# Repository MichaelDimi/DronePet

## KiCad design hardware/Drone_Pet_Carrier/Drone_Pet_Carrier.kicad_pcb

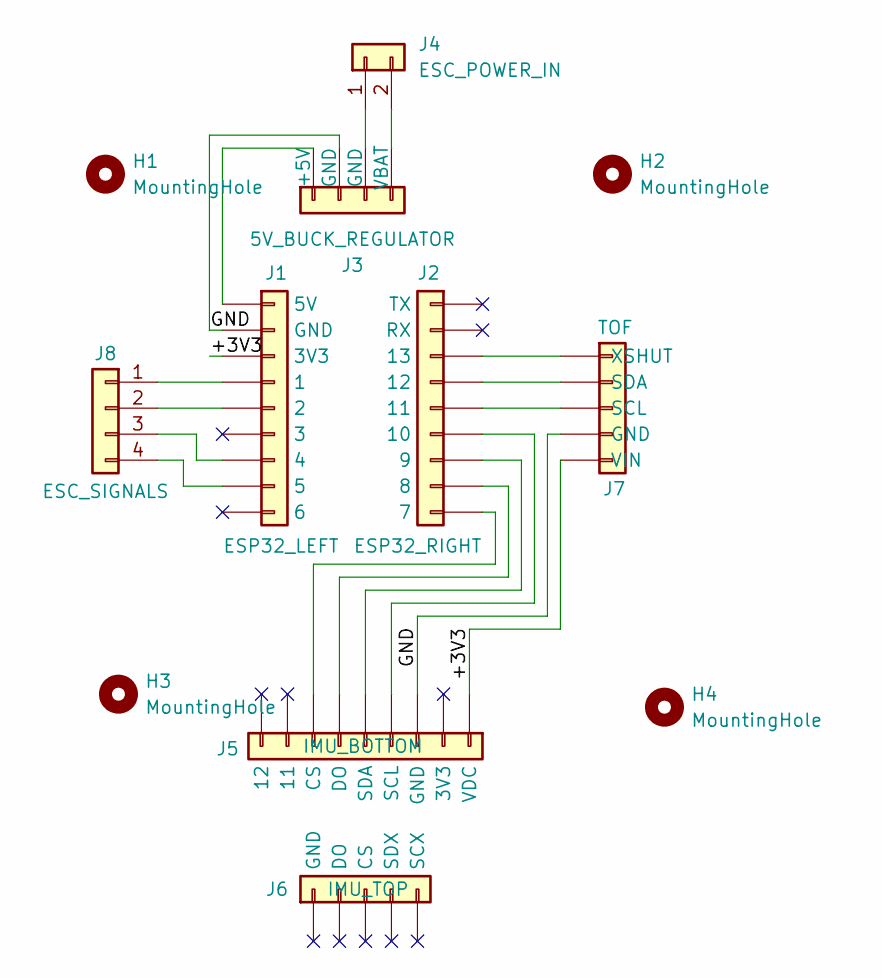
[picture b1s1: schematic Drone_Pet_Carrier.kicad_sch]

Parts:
H1, H2, H3, H4: MountingHole; MountingHole_3.2mm_M3
J1: ESP32_LEFT; PinSocket_1x09_P2.54mm_Vertical
J2: ESP32_RIGHT; PinSocket_1x09_P2.54mm_Vertical
J3: 5V_BUCK_REGULATOR; Buck_Regulator_4Pad_P2.54mm
J4: ESC_POWER_IN
J5: IMU_BOTTOM; PinSocket_1x09_P2.54mm_Vertical
J6: IMU_TOP; PinSocket_1x05_P2.54mm_Vertical
J7: TOF; PinSocket_1x05_P2.54mm_Vertical
J8: ESC_SIGNALS; PinSocket_1x04_P2.54mm_Vertical

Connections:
/+3V3: J1.3 (3V3), J5.1 (VDC), J7.5 (VIN)
/GND: J1.2 (GND), J3.2 (GND), J5.3 (GND), J7.4 (GND)
unnamed: J1.4 (1), J8.1
unnamed: J1.5 (2), J8.2
unnamed: J1.7 (4), J8.3
unnamed: J1.8 (5), J8.4
unnamed: J1.1 (5V), J3.1 (+5V)
unnamed: J2.9 (7), J5.7 (CS)
unnamed: J2.7 (9), J5.5 (SDA)
unnamed: J2.6 (10), J5.4 (SCL)
unnamed: J2.5 (11), J7.3 (SCL)
unnamed: J2.4 (12), J7.2 (SDA)
unnamed: J2.3 (13), J7.1 (XSHUT)
unnamed: J3.4 (VBAT), J4.2
unnamed: J3.3 (GND), J4.1
unnamed: J2.8, J5.6 (DO)

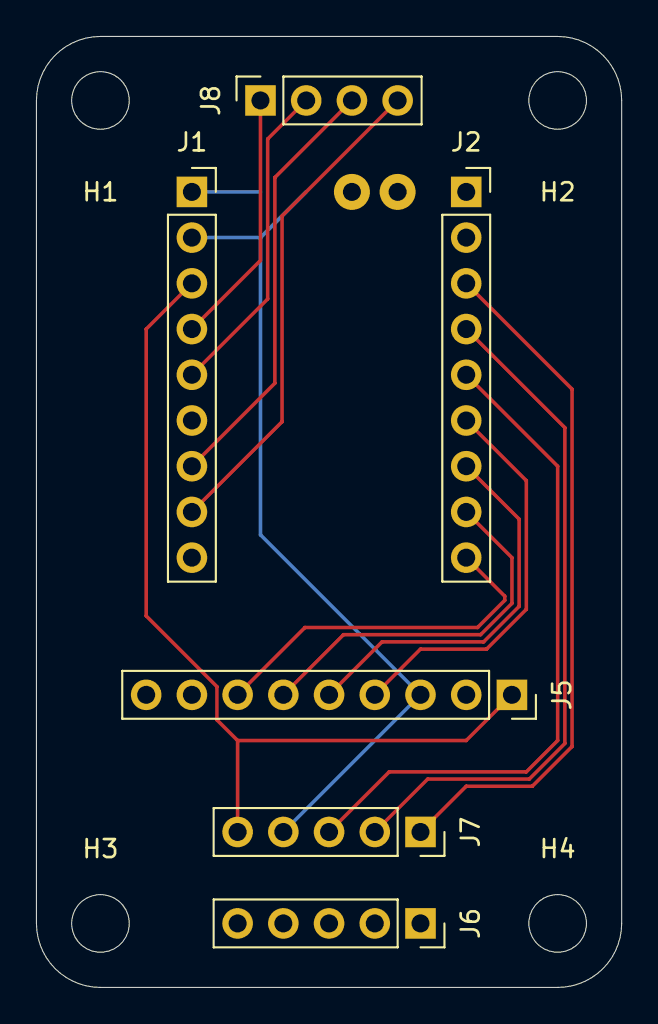
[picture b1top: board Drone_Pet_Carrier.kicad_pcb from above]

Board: 2 copper layers, 32.5 x 52.8 mm, 11 parts (1 on the bottom side), 14 nets.
